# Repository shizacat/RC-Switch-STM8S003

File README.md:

# Description

Reacts to switching the joystick stick switch.

## Principle of work

The input receives a PWM signal from an RC receiver. For different stick positions there will be different duty cycle. By measuring its duration, you can determine the position of the stick and send a signal to the MC output.

# Hardware

Since my option was needed to turn on the LED backlight, I do not use external power and a powerful transistor. I also needed only one position.

# Firwmware

SDCC is used for compilation. You also need STM8S_SPL from ST - a library for working with peripherals.

## How to flash

I use stm8flash for flash.

First of all, you need to configure Option bytes for hardware. For capturing, the 1st channel of the 1st timer is used (Channel 1 TIM1).

```bash
echo -ne '\x00\x00\xff\x01\xfe\x00\xff\x00\xff\x00\xff' > opt.bin
stm8flash -c stlinkv2 -p stm8s103f3 -s opt -w opt.bin
```

This line activates alternative functions of the leg we need: Port C5 alternate function = TIM2_CH1; port C6 alternate function =TIM1_CH1; port C7 alternate function = TIM1_CH2.

Then we are already flashing the firmware itself (firmware.bin). Here you can already use: make upload, or manually download stm8flash.

```bash
./stm8flash -c stlinkv2 -p stm8s003f3 -w firmware.ihx
```

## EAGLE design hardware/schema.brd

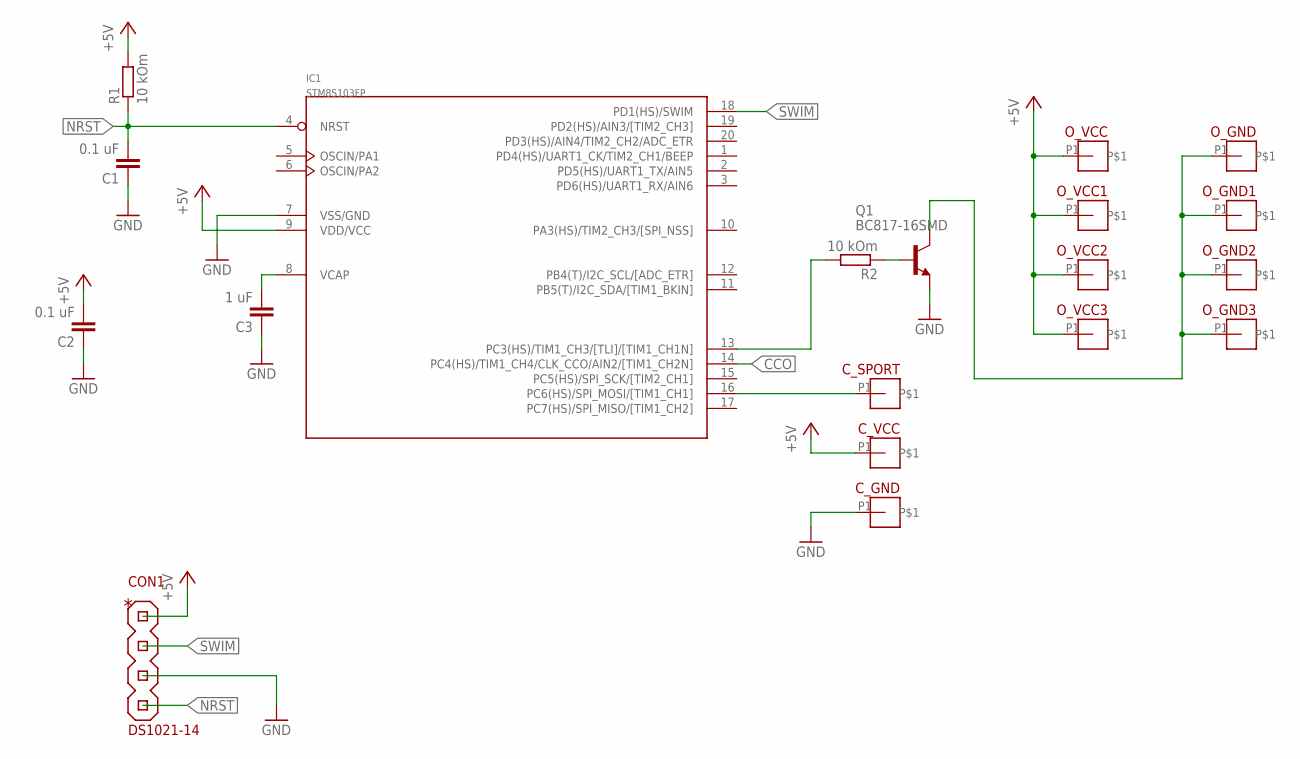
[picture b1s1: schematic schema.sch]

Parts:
C1, C2: 0.1 uF; C0603
C3: 1 uF; C0603
CON1: DS1021-14; DS1021-1*4
C_GND: PAD1_0.8
C_SPORT: PAD1_0.8
C_VCC: PAD1_0.8
IC1: STM8S103FP; TSSOP20
O_GND, O_GND1, O_GND2, O_GND3: PAD1_0.8
O_VCC, O_VCC1, O_VCC2, O_VCC3: PAD1_0.8
Q1: BC817-16SMD; SOT23-BEC
R1, R2: 10 kOm; R0603

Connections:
+5V: C2.2, CON1.P1, C_VCC.P1, IC1.9 (VDD/VCC), O_VCC.P1, O_VCC1.P1, O_VCC2.P1, O_VCC3.P1, R1.2
CCO: IC1.14 (PC4(HS)/TIM1_CH4/CLK_CCO/AIN2/[TIM1_CH2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)
GND: C1.1, C2.1, C3.1, CON1.P3, C_GND.P1, IC1.7 (VSS/GND), Q1.E
unnamed: C_SPORT.P1, IC1.16 (PC6(HS)/SPI_MOSI/[TIM1_CH1])
unnamed: C3.2, IC1.8 (VCAP)
unnamed: O_GND.P1, O_GND1.P1, O_GND2.P1, O_GND3.P1, Q1.C
unnamed: IC1.13 (PC3(HS)/TIM1_CH3/[TLI]/[TIM1_CH1N]), R2.2
unnamed: Q1.B, R2.1
NRST: C1.2, CON1.P4, IC1.4 (NRST), R1.1
SWIM: CON1.P2, IC1.18 (PD1(HS)/SWIM)

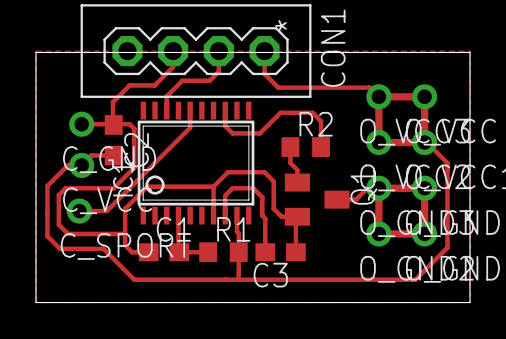
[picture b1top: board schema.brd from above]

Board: 2 copper layers, 24.1 x 13.9 mm, 19 parts (0 on the bottom side), 9 nets.

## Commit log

2020-02-23 ignore
2020-02-23 hardware
2020-02-23 firmware
2020-02-23 readme
2020-02-23 Translate readme
2020-02-24 Clear code
